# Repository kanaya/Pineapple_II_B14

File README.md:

Pineapple_II_B14
================

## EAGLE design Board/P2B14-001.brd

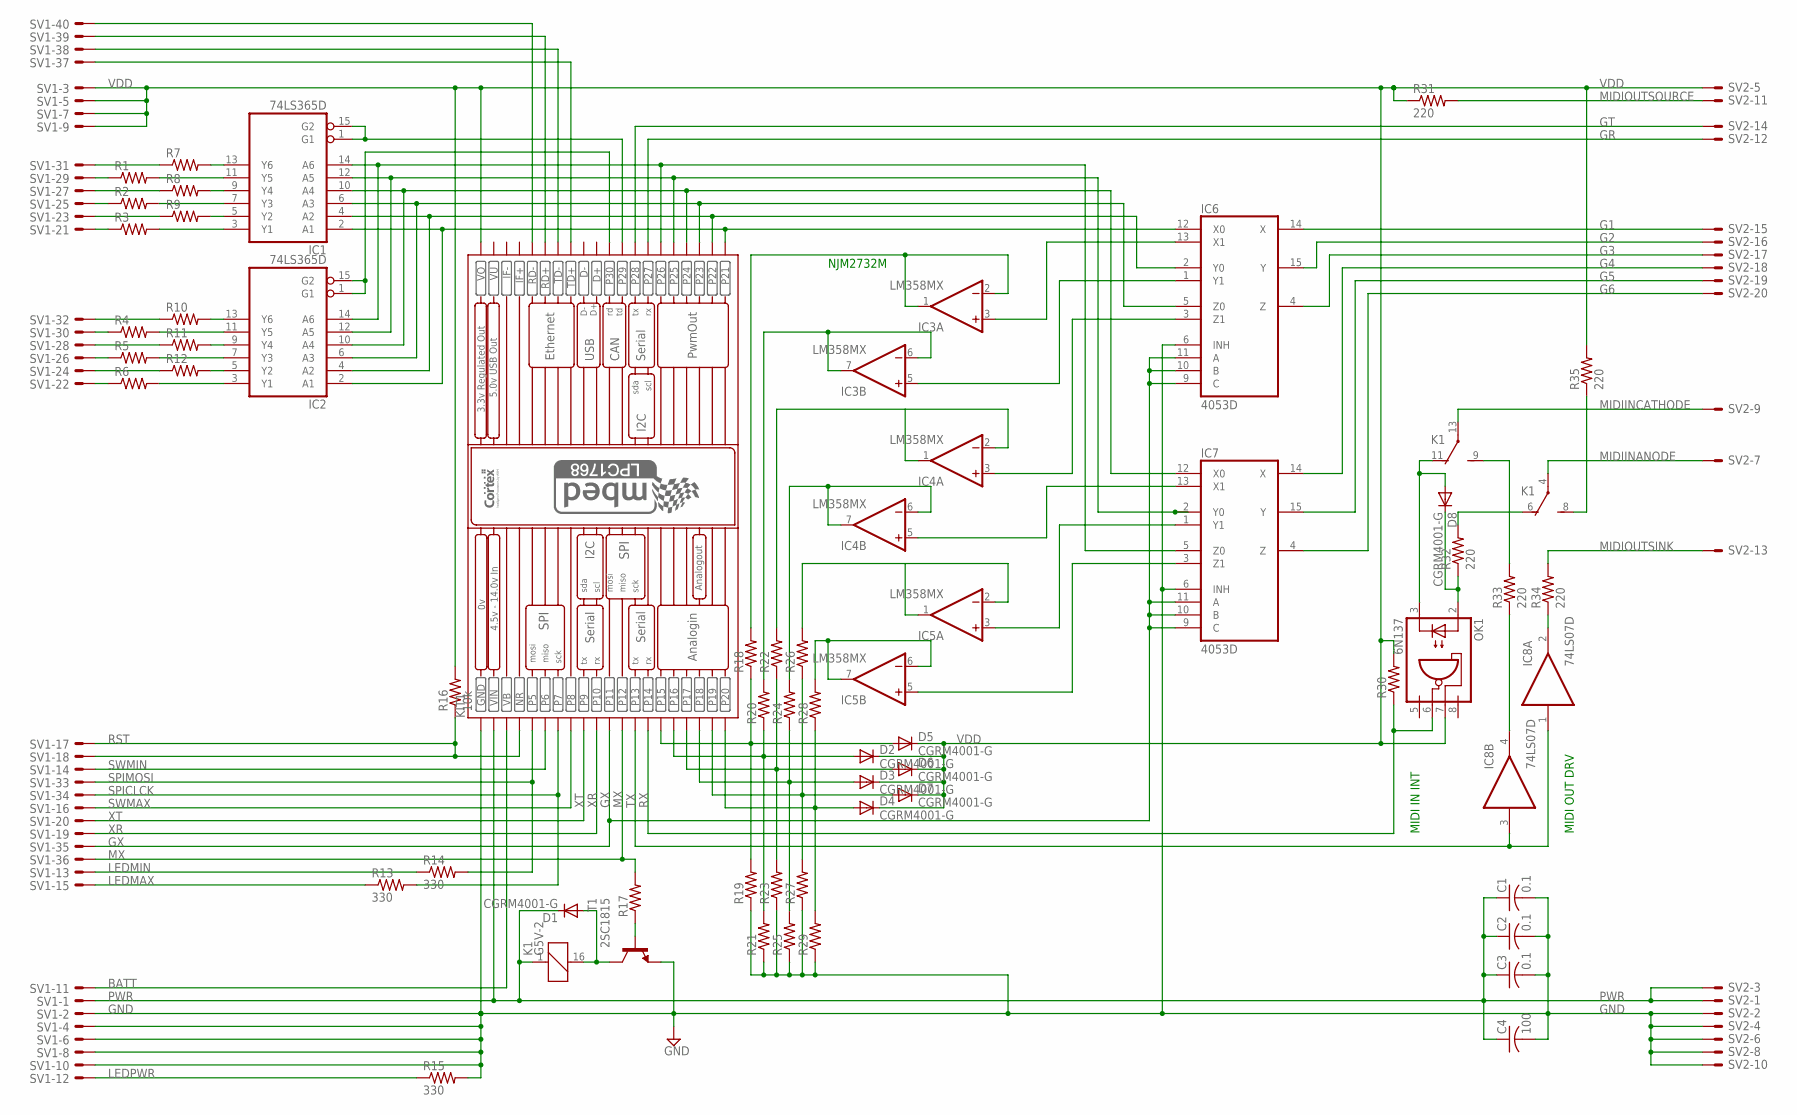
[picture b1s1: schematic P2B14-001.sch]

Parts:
C1, C2, C3: 0.1; C0402
C4: 100; C025-050X050
D1, D2, D3, D4, D5, D6, D7, D8: CGRM4001-G; SOD-123_MINI-SMA
IC1, IC2: 74LS365D; SO16
IC3, IC4, IC5: LM358MX; SO08
IC6, IC7: 4053D; SO16
IC8: 74LS07D; SO14
K1: G5V-2
KIT1: MBED_NXP_LPC1768; MBED-KIT
OK1: 6N137; DIL08
R1, R2, R3, R4, R5, R6, R7, R8, R9, R10, R11, R12, R17, R18, R19, R20, R21, R22, R23, R24, R25, R26, R27, R28, R29, R30: R-US_M0805; M0805
R13, R14, R15: 330; M0805
R16: 10k; M0805
R31, R32, R33, R34, R35: 220; M0805
SV1: ML40E; ML40
SV2: ML20LE; ML20L
T1: 2SC1815; TO92-ECB

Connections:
BATT: KIT1.VB, SV1.11
G1: IC6.14 (X), SV2.15
G2: IC6.15 (Y), SV2.16
G3: IC6.4 (Z), SV2.17
G4: IC7.14 (X), SV2.18
G5: IC7.15 (Y), SV2.19
G6: IC7.4 (Z), SV2.20
GND: C1.2, C2.2, C3.2, C4.2, IC1.8 (GND), IC2.8 (GND), IC6.6 (INH), IC6.8 (GND), IC7.6 (INH), IC7.8 (GND), IC8.7 (GND), KIT1.GND, R15.2, R19.1, R21.1, R23.1, R25.1, R27.1, R29.1, SV1.2, SV1.4, SV1.6, SV1.8, SV1.10, SV2.2, SV2.4, SV2.6, SV2.8, SV2.10, T1.E
GR: KIT1.P$27 (P27), SV2.12
GT: KIT1.P$28 (P28), SV2.14
GX: IC6.9 (C), IC6.10 (B), IC6.11 (A), IC7.9 (C), IC7.10 (B), IC7.11 (A), KIT1.P$11 (P11), SV1.35
LEDMAX: R13.1, SV1.15
LEDMIN: R14.1, SV1.13
LEDPWR: R15.1, SV1.12
MIDIINANODE: K1.4, SV2.7
MIDIINCATHODE: K1.13, SV2.9
MIDIOUTSINK: R34.2, SV2.13
MIDIOUTSOURCE: R31.2, SV2.11
MX: KIT1.P$12 (P12), R17.2, SV1.36
unnamed: IC1.2 (A1), IC2.2 (A1), IC6.12 (X0), KIT1.P$21 (P21)
unnamed: K1.6 (O), R32.2
unnamed: IC3.6 (-IN), IC3.7 (OUT), R20.2
unnamed: IC1.13 (Y6), R7.2
unnamed: K1.8 (S), R35.1
unnamed: D1.A, K1.16 (2), T1.C
unnamed: IC8.4 (O), R33.1
unnamed: IC8.2 (O), R34.1
unnamed: IC1.6 (A3), IC2.6 (A3), IC6.5 (Z0), KIT1.P$23 (P23)
unnamed: K1.9 (S), R33.2
unnamed: D3.A, KIT1.P$18 (P18), R24.1, R25.2
unnamed: IC1.10 (A4), IC2.10 (A4), IC7.12 (X0), KIT1.P$24 (P24)
unnamed: IC1.11 (Y5), R1.2
unnamed: IC1.4 (A2), IC2.4 (A2), IC6.2 (Y0), KIT1.P$22 (P22)
unnamed: IC1.9 (Y4), R8.2
unnamed: IC1.7 (Y3), R2.2
unnamed: IC1.5 (Y2), R9.2
unnamed: IC4.1 (OUT), IC4.2 (-IN), R22.2
unnamed: R17.1, T1.B
unnamed: IC1.3 (Y1), R3.2
unnamed: IC2.13 (Y6), R10.2
unnamed: D8.C, OK1.2 (A), R32.1
unnamed: IC2.1 (G1), IC2.15 (G2), KIT1.P$30 (P30)
unnamed: IC1.1 (G1), IC1.15 (G2), KIT1.P$29 (P29)
unnamed: IC2.11 (Y5), R4.2
unnamed: IC2.9 (Y4), R11.2
unnamed: D8.A, K1.11 (O), OK1.3 (C)
unnamed: IC2.7 (Y3), R5.2
unnamed: IC2.5 (Y2), R12.2
unnamed: IC2.3 (Y1), R6.2
unnamed: R3.1, SV1.21
unnamed: R6.1, SV1.22
unnamed: IC1.12 (A5), IC2.12 (A5), IC7.2 (Y0), KIT1.P$25 (P25)
unnamed: IC1.14 (A6), IC2.14 (A6), IC7.5 (Z0), KIT1.P$26 (P26)
unnamed: D5.A, KIT1.P$15 (P15), R18.1, R19.2
unnamed: D2.A, KIT1.P$16 (P16), R20.1, R21.2
unnamed: D6.A, KIT1.P$17 (P17), R22.1, R23.2
unnamed: IC4.6 (-IN), IC4.7 (OUT), R24.2
unnamed: D7.A, KIT1.P$19 (P19), R26.1, R27.2
unnamed: D4.A, KIT1.P$20 (P20), R28.1, R29.2
unnamed: R9.1, SV1.23
unnamed: IC5.1 (OUT), IC5.2 (-IN), R26.2
unnamed: IC5.6 (-IN), IC5.7 (OUT), R28.2
unnamed: R12.1, SV1.24
unnamed: R2.1, SV1.25
unnamed: R5.1, SV1.26
unnamed: R8.1, SV1.27
unnamed: R11.1, SV1.28
unnamed: R1.1, SV1.29
unnamed: R4.1, SV1.30
unnamed: R7.1, SV1.31
unnamed: R10.1, SV1.32
unnamed: KIT1.TD+, SV1.37
unnamed: KIT1.TD-, SV1.38
unnamed: KIT1.RD+, SV1.39
unnamed: KIT1.RD-, SV1.40
unnamed: IC3.1 (OUT), IC3.2 (-IN), R18.2
unnamed: IC3.3 (+IN), IC6.13 (X1)
unnamed: IC3.5 (+IN), IC6.1 (Y1)
unnamed: IC4.3 (+IN), IC6.3 (Z1)
unnamed: IC4.5 (+IN), IC7.13 (X1)
unnamed: IC5.3 (+IN), IC7.1 (Y1)
unnamed: IC5.5 (+IN), IC7.3 (Z1)
PWR: C1.1, C2.1, C3.1, C4.1, D1.C, K1.1, KIT1.VIN, SV1.1, SV2.1, SV2.3
RST: KIT1.NR, R16.1, SV1.17, SV1.18
RX: KIT1.P$14 (P14), OK1.6 (VO), R30.1
SPICLCK: KIT1.P$7 (P7), R13.2, SV1.34
SPIMOSI: KIT1.P$5 (P5), R14.2, SV1.33
SWMAX: KIT1.P$8 (P8), SV1.16
SWMIN: KIT1.P$6 (P6), SV1.14
TX: IC8.1 (I), IC8.3 (I), KIT1.P$13 (P13)
V+: IC3.8 (V+), IC4.8 (V+), IC5.8 (V+)
V-: IC3.4 (V-), IC4.4 (V-), IC5.4 (V-)
VCC: IC1.16 (VCC), IC2.16 (VCC), IC6.16 (VCC), IC7.16 (VCC), IC8.14 (VCC)
VDD: D2.C, D3.C, D4.C, D5.C, D6.C, D7.C, KIT1.VOUT (VO), OK1.7 (VE), R16.2, R30.2, R31.1, R35.2, SV1.3, SV1.5, SV1.7, SV1.9, SV2.5
VEE: IC6.7 (VEE), IC7.7 (VEE)
VU: KIT1.VU
XR: KIT1.P$10 (P10), SV1.19
XT: KIT1.P$9 (P9), SV1.20

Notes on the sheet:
MIDI OUT DRV
MIDI IN INT
NJM2732M

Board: 2 copper layers, 61 parts (0 on the bottom side), 97 nets, no tracks yet.

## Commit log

2014-11-27 Imported from C14.
